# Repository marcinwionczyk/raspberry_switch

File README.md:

# raspberry_switch
A switch to turn on and truly turn off raspberry Pi (Zero).

## How it works

From schematic point of view, it look like this:

When SW2 switch is pressed, NE555 will keep power on for approximately 24 seconds.
During this time, Raspberry Pi will boot and start service 
[relay_switch_on](software/lib/systemd/system/relay_switch_on.service) which set pin GPIO12 as output with high state.
 
When Pi is halted, service [relay_switch_off](software/lib/systemd/system/relay_switch_off.service) will set GPIO12 to 
low and effectively cut off the power. 

## Hardware
I have designed PCB with Autodesk Eagle. You may download and change according to your liking: 
* [schematics](hardware/Autodesk%20Eagle%20project/main.sch), 
* [board](hardware/Autodesk%20Eagle%20project/main.brd)

There are also [gerber files](hardware/gerber_files.zip)

## How to install
1. Copy everything from software folder into your root folder
1. Make python scripts executable:
    1. `sudo chmod +x /usr/local/bin/relayOff.py` 
    1. `sudo chmod +x /usr/local/bin/relayOn.py`
1. Execute below commands:
    1. `systemctl daemon-reload`
    1. `systemctl enable relay_switch_on`
    1. `systemctl enable relay_switch_off`
1. Connect pin GPIO12 with wire to signal "KEEP_POWER_ON".
1. Power off
1. Plug usb output from power adapter into X3 connector
1. Connect with usb cable X1 connector and raspberry pi input power

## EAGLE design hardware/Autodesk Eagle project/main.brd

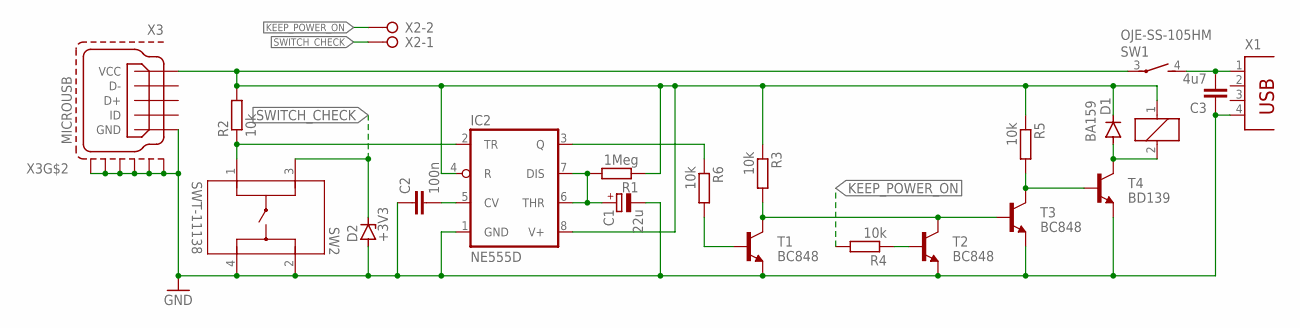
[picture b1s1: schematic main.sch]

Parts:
C1: 22u; SMC_B
C2: 100n; C0805
C3: 4u7; C050-075X075
D1: BA159; DO41-10
D2: +3V3; SOD80C
IC2: NE555D; SO08
R1: 1Meg; R1206
R2, R3, R4, R5, R6: 10k; R1206
SW1: OJE-SS-105HM
SW2: SWT-11138
T1, T2, T3: BC848; SOT23
T4: BD139; TO126
X1: PN87520
X2: W237-02P; W237-132
X3: MICROUSB

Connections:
+5V: D1.C, IC2.4 (R), IC2.8 (V+), R1.1, R2.2, R3.1, R5.1, SW1.1, SW1.3, X3.1 (VCC)
GND: C1.-, C2.1, C3.1, D2.A, IC2.1 (GND), SW2.2 (4), SW2.4 (3), T1.2 (E), T2.2 (E), T3.2 (E), T4.1 (E), X1.4, X3.5 (GND), X3.P$1 (S1), X3.P$2 (S2), X3.P$3 (S3), X3.P$4 (S4), X3.P$5 (S5), X3.P$6 (S6)
KEEP_POWER_ON: R4.2, X2.2
unnamed: C1.+, IC2.6 (THR), IC2.7 (DIS), R1.2
unnamed: R6.2, T1.1 (B)
unnamed: C2.2, IC2.5 (CV)
unnamed: IC2.2 (TR), R2.1, SW2.1
unnamed: IC2.3 (Q), R6.1
unnamed: R5.2, T3.3 (C), T4.3 (B)
unnamed: C3.2, SW1.4 (S), X1.1
unnamed: R4.1, T2.1 (B)
unnamed: R3.2, T1.3 (C), T2.3 (C), T3.1 (B)
unnamed: D1.A, SW1.2, T4.2 (C)
SWITCH_CHECK: D2.C, SW2.3 (2), X2.1

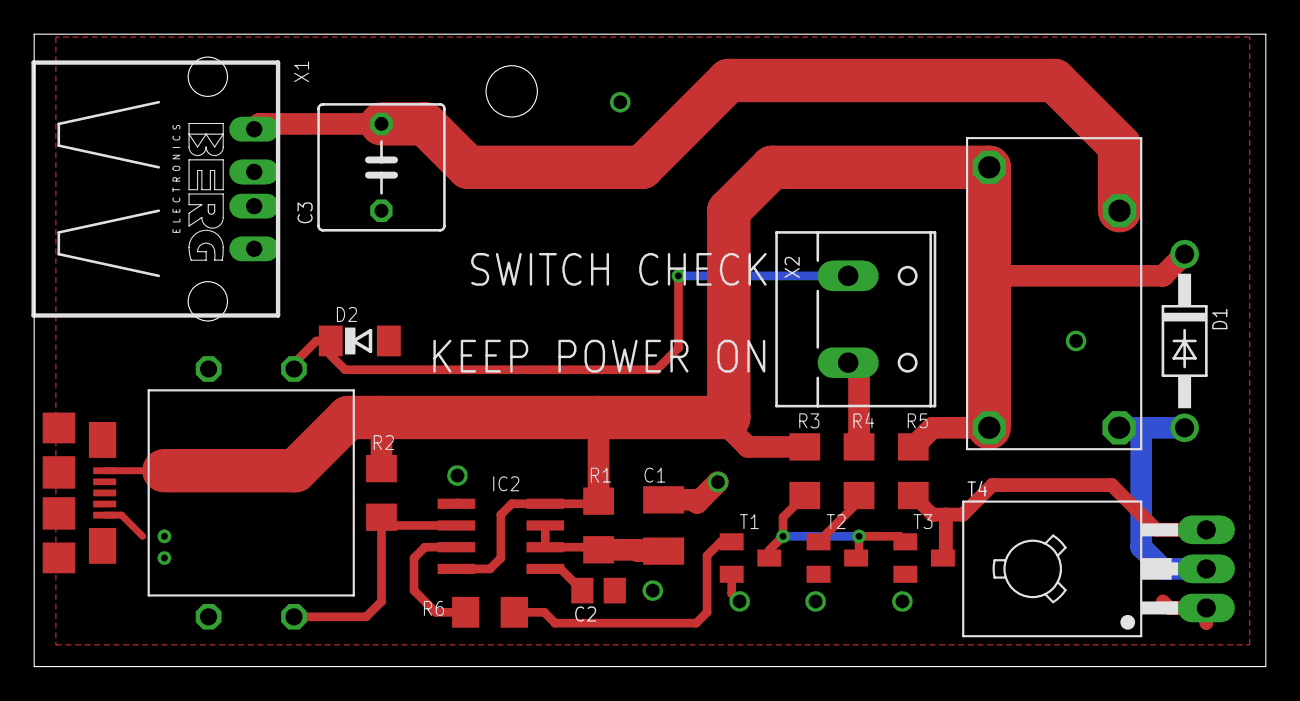
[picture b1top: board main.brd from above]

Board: 2 copper layers, 72.1 x 37.0 mm, 21 parts (0 on the bottom side), 14 nets.

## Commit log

2020-03-11 Removed "SWITCH_CHECK" signal. Does not work as expected. Somehow it turns on Raspberry Pi.
    Added gerber files
2020-03-11 removed sensing input on GPIO6 pin
